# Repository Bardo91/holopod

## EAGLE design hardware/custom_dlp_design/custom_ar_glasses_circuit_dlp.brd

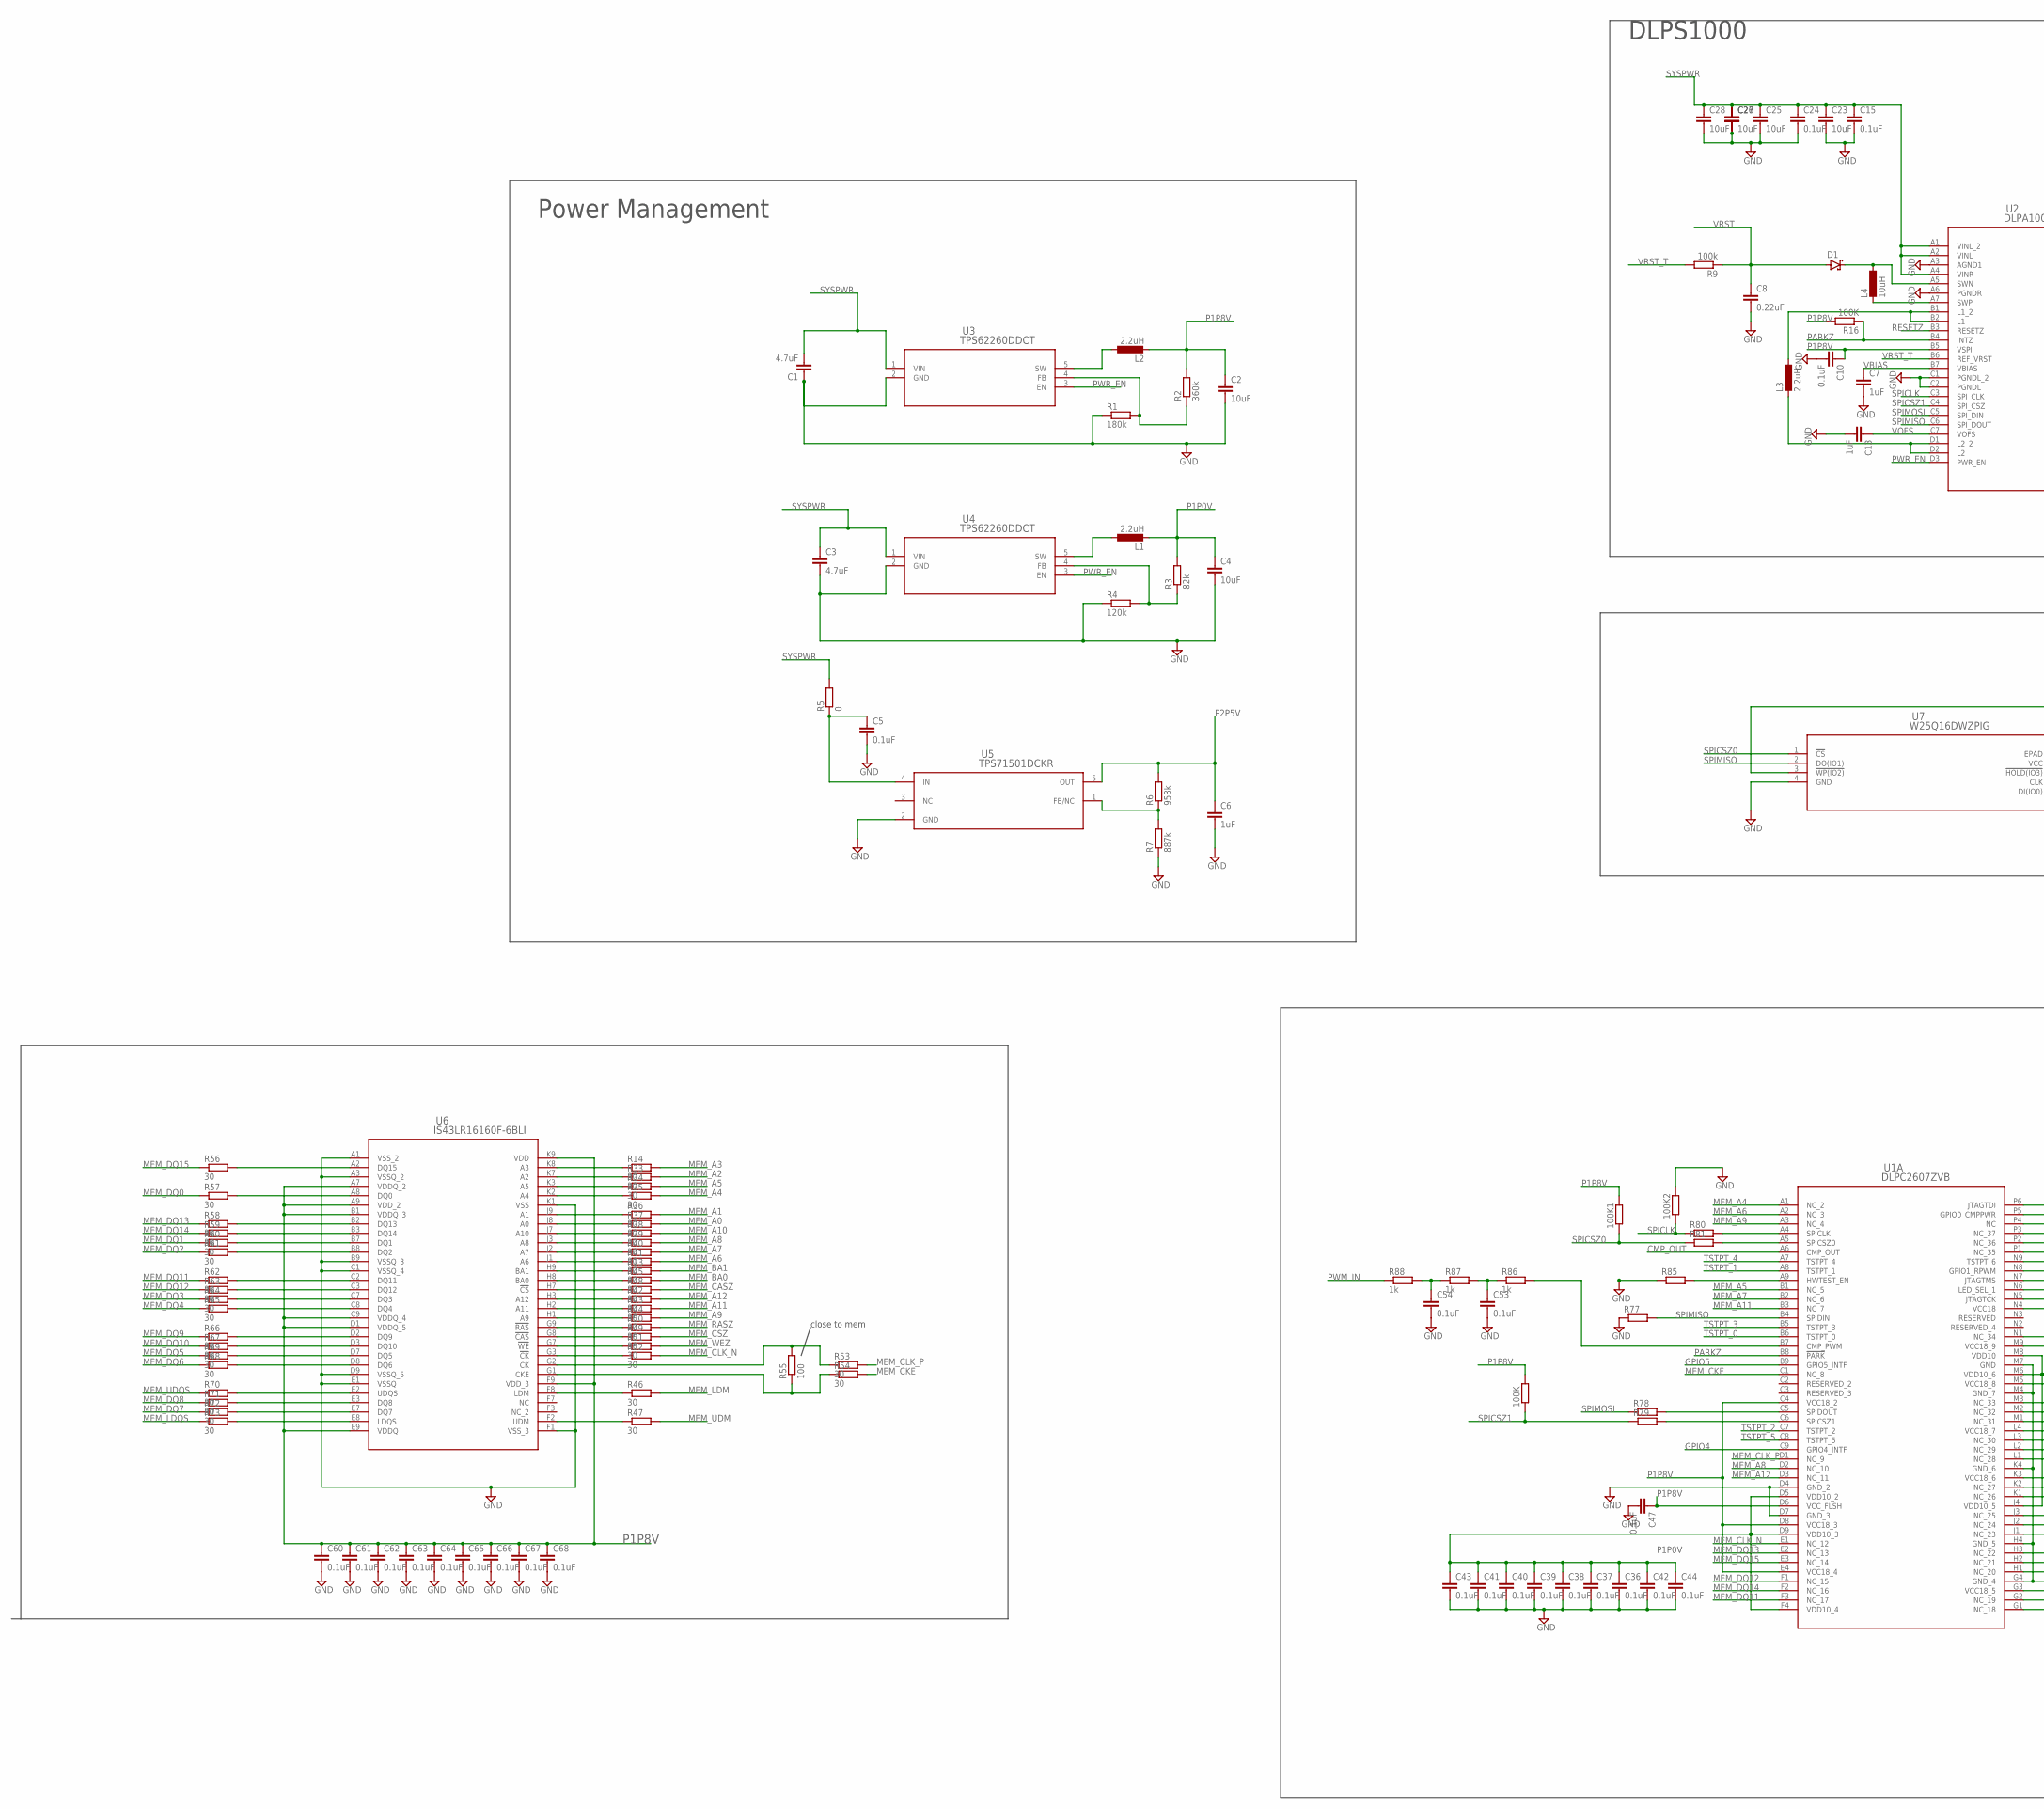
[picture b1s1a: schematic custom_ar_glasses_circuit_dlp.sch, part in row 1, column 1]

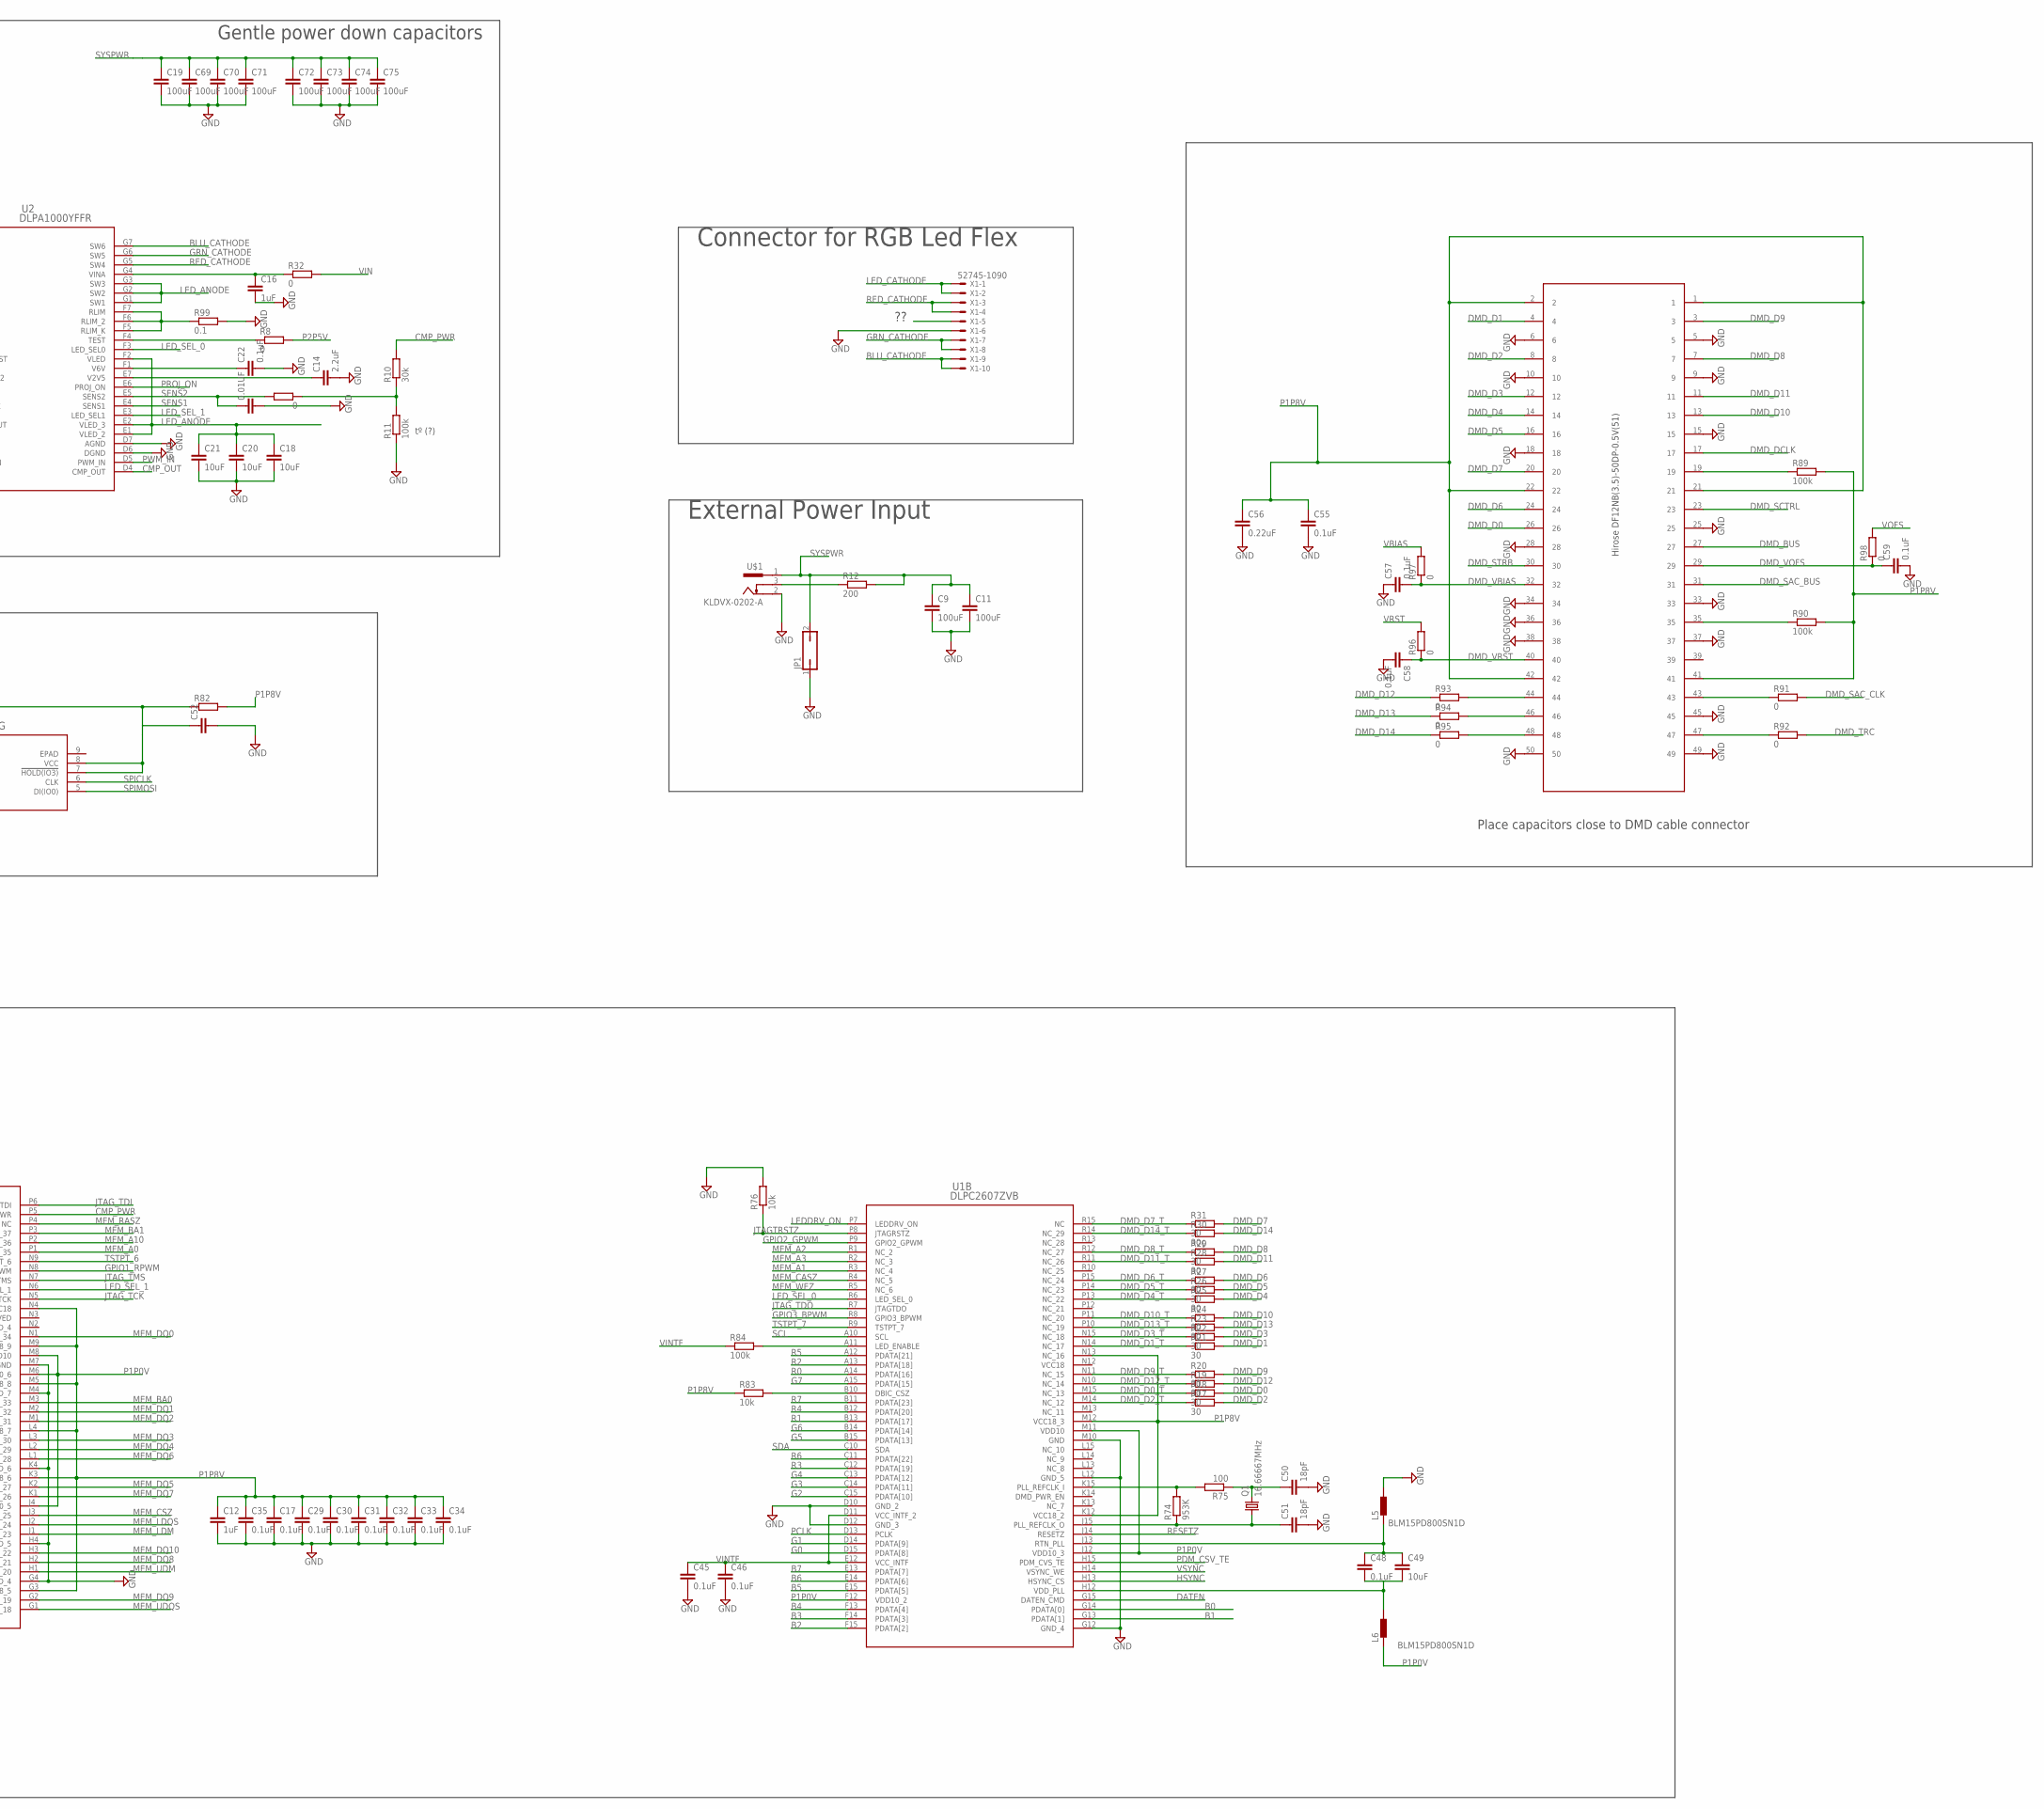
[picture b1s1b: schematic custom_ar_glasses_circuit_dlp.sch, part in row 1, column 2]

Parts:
0, 100K, 100K1, 100K2: R-EU_R0201; R0201
0.01UF: C-EUC0201; C0201
C1, C3: 4.7uF; C0201
C2, C4, C18, C20, C21, C23, C25, C27, C28, C49: 10uF; C0201
C5, C10, C15, C17, C22, C24, C29, C30, C31, C32, C33, C34, C35, C36, C37, C38, C39, C40, C41, C42, C43, C44, C45, C46, C47, C48, C53, C54, C55, C57, C58, C59, C60, C61, C62, C63, C64, C65, C66, C67, C68: 0.1uF; C0201
C6, C7, C12, C13, C16: 1uF; C0201
C8, C56: 0.22uF; C0201
C9, C11: 100uF; C1206K
C14: 2.2uF; C0201
C19, C69, C70, C71, C72, C73, C74, C75: 100uF; C0805
C26, C52: C-EUC0201; C0201
C50, C51: 18pF; C0201
D1: SCHOTTKY-DIODESMC; SMC
JP1: JP1Q; JP1
L1, L2, L3: 2.2uH; L3225M
L4: 10uH; L3216C
L5, L6: BLM15PD800SN1D; 0402
Q1: 16.66667MHz; MC-405
R1: 180k; R0201
R2: 360k; R0201
R3: 82k; R0201
R4: 120k; R0201
R5, R8, R32, R91, R92, R93, R94, R95, R96, R97, R98: 0; R0201
R6: 953k; R0201
R7: 887k; R0201
R9, R11, R84, R89, R90: 100k; R0201
R10: 30k; R0201
R12: 200; R1206
R13, R14, R17, R18, R19, R20, R21, R22, R23, R24, R25, R26, R27, R28, R29, R31, R33, R34, R35, R36, R37, R38, R39, R40, R41, R42, R43, R44, R45, R46, R47, R48, R49, R50, R51, R52, R53, R54, R56, R57, R58, R59, R60, R61, R62, R63, R64, R65, R66, R67, R68, R69, R70, R71, R72, R73: 30; R0201
R16: 100K; R0201
R30: 30ç; R0201
R55, R75: 100; R0201
R74: 953K; R0201
R76, R83: 10k; R0201
R77, R78, R79, R80, R81, R82, R85: R-EU_R0201; R0201
R86, R87, R88: 1k; R0201
R99: 0.1; R0201
U1: DLPC2607ZVB; ZVB176_TEX
U2: DLPA1000YFFR; YFF49_TEX
U3, U4: TPS62260DDCT; DDC5
U5: TPS71501DCKR; DCK5
U6: IS43LR16160F-6BLI; TFBGA-60_8X10_ISI
U7: W25Q16DWZPIG; WIN_ZP-8_WIN
U$1: KLDVX-0202-A
U$2: HIROSEDF12NB(3.5)-50DP-0.5V(51)
X1: 52745-1090

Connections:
B0: U1.G14 (PDATA[0])
B1: U1.G13 (PDATA[1])
B2: U1.F15 (PDATA[2])
B3: U1.F14 (PDATA[3])
B4: U1.F13 (PDATA[4])
B5: U1.E15 (PDATA[5])
B6: U1.E14 (PDATA[6])
B7: U1.E13 (PDATA[7])
BLU_CATHODE: U2.G7 (SW6), X1.9, X1.10
CMP_OUT: U1.A6 (CMP_OUT), U2.D4 (CMP_OUT)
CMP_PWR: R10.2, U1.P5 (GPIO0_CMPPWR)
DATEN: U1.G15 (DATEN_CMD)
DMD_BUS: U$2.27
DMD_D0: R18.2, U$2.26
DMD_D0_T: R18.1, U1.M15 (NC_13)
DMD_D1: R21.2, U$2.4
DMD_D1_T: R21.1, U1.N14 (NC_17)
DMD_D2: R17.2, U$2.8
DMD_D2_T: R17.1, U1.M14 (NC_12)
DMD_D3: R22.2, U$2.12
DMD_D3_T: R22.1, U1.N15 (NC_18)
DMD_D4: R25.2, U$2.14
DMD_D4_T: R25.1, U1.P13 (NC_22)
DMD_D5: R26.2, U$2.16
DMD_D5_T: R26.1, U1.P14 (NC_23)
DMD_D6: R27.2, U$2.24
DMD_D6_T: R27.1, U1.P15 (NC_24)
DMD_D7: R31.2, U$2.20
DMD_D7_T: R31.1, U1.R15 (NC)
DMD_D8: R29.2, U$2.7
DMD_D8_T: R29.1, U1.R12 (NC_27)
DMD_D9: R20.2, U$2.3
DMD_D9_T: R20.1, U1.N11 (NC_15)
DMD_D10: R24.2, U$2.13
DMD_D10_T: R24.1, U1.P11 (NC_20)
DMD_D11: R28.2, U$2.11
DMD_D11_T: R28.1, U1.R11 (NC_26)
DMD_D12: R19.2, R93.1
DMD_D12_T: R19.1, U1.N10 (NC_14)
DMD_D13: R23.2, R94.1
DMD_D13_T: R23.1, U1.P10 (NC_19)
DMD_D14: R30.2, R95.1
DMD_D14_T: R30.1, U1.R14 (NC_29)
DMD_DCLK: U$2.17
DMD_SAC_BUS: U$2.31
DMD_SAC_CLK: R91.2
DMD_SCTRL: U$2.23
DMD_STRB: U$2.30
DMD_TRC: R92.2
DMD_VBIAS: C57.2, R97.1, U$2.32
DMD_VOFS: C59.1, R98.1, U$2.29
DMD_VRST: C58.1, R96.1, U$2.40
G0: U1.D15 (PDATA[8])
G1: U1.D14 (PDATA[9])
G2: U1.C15 (PDATA[10])
G3: U1.C14 (PDATA[11])
G4: U1.C13 (PDATA[12])
G5: U1.B15 (PDATA[13])
G6: U1.B14 (PDATA[14])
G7: U1.A15 (PDATA[15])
GND: 0.01UF.2, 100K2.2, C1.1, C2.2, C3.2, C4.2, C5.2, C6.2, C7.2, C8.2, C9.2, C10.2, C11.2, C12.2, C13.2, C14.2, C15.2, C16.2, C17.2, C18.2, C19.2, C20.2, C21.2, C22.2, C23.2, C24.2, C25.2, C26.2, C27.2, C28.2, C29.2, C30.2, C31.2, C32.2, C33.2, C34.2, C35.2, C36.2, C37.2, C38.2, C39.2, C40.2, C41.2, C42.2, C43.2, C44.2, C45.2, C46.2, C47.2, C50.2, C51.2, C52.2, C53.2, C54.2, C55.2, C56.2, C57.1, C58.2, C59.2, C60.2, C61.2, C62.2, C63.2, C64.2, C65.2, C66.2, C67.2, C68.2, C69.2, C70.2, C71.2, C72.2, C73.2, C74.2, C75.2, JP1.1, L5.2, R1.1, R4.1, R7.1, R11.1, R76.2, R77.1, R85.1, R99.2, U1.D4 (GND_2), U1.D7 (GND_3), U1.D10 (GND_2), U1.D12 (GND_3), U1.G4 (GND_4), U1.G12 (GND_4), U1.H4 (GND_5), U1.K4 (GND_6), U1.L12 (GND_5), U1.M4 (GND_7), U1.M7 (GND), U1.M10 (GND), U2.A3 (AGND1), U2.A6 (PGNDR), U2.C1 (PGNDL_2), U2.C2 (PGNDL), U2.D6 (DGND), U2.D7 (AGND), U3.2 (GND), U4.2 (GND), U5.2 (GND), U6.A1 (VSS_2), U6.A3 (VSSQ_2), U6.B9 (VSSQ_3), U6.C1 (VSSQ_4), U6.D9 (VSSQ_5), U6.E1 (VSSQ), U6.F1 (VSS_3), U6.K1 (VSS), U7.4 (GND), U$1.2, U$2.5, U$2.6, U$2.9, U$2.10, U$2.15, U$2.18, U$2.25, U$2.28, U$2.33, U$2.34, U$2.36, U$2.37, U$2.38, U$2.45, U$2.49, U$2.50, X1.6
GPIO1_RPWM: U1.N8 (GPIO1_RPWM)
GPIO2_GPWM: U1.P9 (GPIO2_GPWM)
GPIO3_BPWM: U1.R8 (GPIO3_BPWM)
GPIO4: U1.C9 (GPIO4_INTF)
GPIO5: U1.B9 (GPIO5_INTF)
GRN_CATHODE: U2.G6 (SW5), X1.7, X1.8
HSYNC: U1.H13 (HSYNC_CS)
JTAGTRSTZ: R76.1, U1.P8 (JTAGRSTZ)
JTAG_TCK: U1.N5 (JTAGTCK)
JTAG_TDI: U1.P6 (JTAGTDI)
JTAG_TDO: U1.R7 (JTAGTDO)
JTAG_TMS: U1.N7 (JTAGTMS)
LEDDRV_ON: U1.P7 (LEDDRV_ON)
LED_ANODE: C18.1, C20.1, C21.1, U2.E1 (VLED_2), U2.E2 (VLED_3), U2.F2 (VLED), U2.G1 (SW1), U2.G2 (SW2), U2.G3 (SW3)
LED_CATHODE: X1.1, X1.2
LED_SEL_0: U1.R6 (LED_SEL_0), U2.F3 (LED_SEL0)
LED_SEL_1: U1.N6 (LED_SEL_1), U2.E3 (LED_SEL1)
MEM_A0: R37.2, U1.P1 (NC_35)
MEM_A1: R36.2, U1.R3 (NC_4)
MEM_A2: R33.2, U1.R1 (NC_2)
MEM_A3: R14.2, U1.R2 (NC_3)
MEM_A4: R35.2, U1.A1 (NC_2)
MEM_A5: R34.2, U1.B1 (NC_5)
MEM_A6: R41.2, U1.A2 (NC_3)
MEM_A7: R40.2, U1.B2 (NC_6)
MEM_A8: R39.2, U1.D2 (NC_10)
MEM_A9: R44.2, U1.A3 (NC_4)
MEM_A10: R38.2, U1.P2 (NC_36)
MEM_A11: R43.2, U1.B3 (NC_7)
MEM_A12: R42.2, U1.D3 (NC_11)
MEM_BA0: R45.2, U1.M3 (NC_33)
MEM_BA1: R13.2, U1.P3 (NC_37)
MEM_CASZ: R48.2, U1.R4 (NC_5)
MEM_CKE: R54.2, U1.C1 (NC_8)
MEM_CLK_N: R52.2, U1.E1 (NC_12)
MEM_CLK_P: R53.2, U1.D1 (NC_9)
MEM_CSZ: R49.2, U1.J3 (NC_25)
MEM_DQ0: R57.1, U1.N1 (NC_34)
MEM_DQ1: R60.1, U1.M2 (NC_32)
MEM_DQ2: R61.1, U1.M1 (NC_31)
MEM_DQ3: R64.1, U1.L3 (NC_30)
MEM_DQ4: R65.1, U1.L2 (NC_29)
MEM_DQ5: R69.1, U1.K2 (NC_27)
MEM_DQ6: R68.1, U1.L1 (NC_28)
MEM_DQ7: R72.1, U1.K1 (NC_26)
MEM_DQ8: R71.1, U1.H2 (NC_21)
MEM_DQ9: R66.1, U1.G2 (NC_19)
MEM_DQ10: R67.1, U1.H3 (NC_22)
MEM_DQ11: R62.1, U1.F3 (NC_17)
MEM_DQ12: R63.1, U1.F1 (NC_15)
MEM_DQ13: R58.1, U1.E2 (NC_13)
MEM_DQ14: R59.1, U1.F2 (NC_16)
MEM_DQ15: R56.1, U1.E3 (NC_14)
MEM_LDM: R46.2, U1.J1 (NC_23)
MEM_LDQS: R73.1, U1.J2 (NC_24)
MEM_RASZ: R50.2, U1.P4 (NC)
MEM_UDM: R47.2, U1.H1 (NC_20)
MEM_UDQS: R70.1, U1.G1 (NC_18)
MEM_WEZ: R51.2, U1.R5 (NC_6)
unnamed: R1.2, R2.1, U3.4 (FB)
unnamed: C22.1, U2.F1 (V6V)
unnamed: L2.1, U3.5 (SW)
unnamed: R8.1, U2.F4 (TEST)
unnamed: L1.1, U4.5 (SW)
unnamed: R99.1, U2.F5 (RLIM_K), U2.F6 (RLIM_2), U2.F7 (RLIM)
unnamed: R3.1, R4.2, U4.4 (FB)
unnamed: C5.1, R5.1, U5.4 (IN)
unnamed: C14.1, U2.E7 (V2V5)
unnamed: R6.1, R7.2, U5.1 (FB/NC)
unnamed: L4.2, U2.A7 (SWP)
unnamed: D1.C, L4.1, U2.A5 (SWN)
unnamed: R36.1, U6.J9 (A1)
unnamed: 0.1, R10.1, R11.2
unnamed: R12.1, U$1.3
unnamed: C16.1, R32.1, U2.G4 (VINA)
unnamed: R35.1, U6.K2 (A4)
unnamed: C48.1, C49.1, L5.1, U1.J13 (RTN_PLL)
unnamed: C48.2, C49.2, L6.2, U1.H12 (VDD_PLL)
unnamed: R14.1, U6.K8 (A3)
unnamed: R13.1, U6.H9 (BA1)
unnamed: R34.1, U6.K3 (A5)
unnamed: R33.1, U6.K7 (A2)
unnamed: L3.1, U2.B1 (L1_2), U2.B2 (L1)
unnamed: L3.2, U2.D1 (L2_2), U2.D2 (L2)
unnamed: R40.1, U6.J2 (A7)
unnamed: R39.1, U6.J3 (A8)
unnamed: R38.1, U6.J7 (A10)
unnamed: R43.1, U6.H2 (A11)
unnamed: R37.1, U6.J8 (A0)
unnamed: R41.1, U6.J1 (A6)
unnamed: R42.1, U6.H3 (A12)
unnamed: R44.1, U6.H1 (A9)
unnamed: R45.1, U6.H8 (BA0)
unnamed: R46.1, U6.F8 (LDM)
unnamed: R47.1, U6.F2 (UDM)
unnamed: R49.1, U6.G8 (!CAS)
unnamed: R48.1, U6.H7 (!CS)
unnamed: R50.1, U6.G9 (!RAS)
unnamed: R51.1, U6.G7 (!WE)
unnamed: R52.1, U6.G3 (!CK)
unnamed: R53.1, R55.2, U6.G2 (CK)
unnamed: R54.1, R55.1, U6.G1 (CKE)
unnamed: R74.2, R75.2, U1.K15 (PLL_REFCLK_I)
unnamed: C51.1, Q1.1, R74.1, U1.J15 (PLL_REFCLK_O)
unnamed: C50.1, Q1.2, R75.1
unnamed: R78.2, U1.C5 (SPIDOUT)
unnamed: R79.2, U1.C6 (SPICSZ1)
unnamed: R80.2, U1.A4 (SPICLK)
unnamed: R56.2, U6.A2 (DQ15)
unnamed: R57.2, U6.A8 (DQ0)
unnamed: R58.2, U6.B2 (DQ13)
unnamed: R59.2, U6.B3 (DQ14)
unnamed: R60.2, U6.B7 (DQ1)
unnamed: R61.2, U6.B8 (DQ2)
unnamed: R62.2, U6.C2 (DQ11)
unnamed: R63.2, U6.C3 (DQ12)
unnamed: R64.2, U6.C7 (DQ3)
unnamed: R65.2, U6.C8 (DQ4)
unnamed: R66.2, U6.D2 (DQ9)
unnamed: R67.2, U6.D3 (DQ10)
unnamed: R69.2, U6.D7 (DQ5)
unnamed: R68.2, U6.D8 (DQ6)
unnamed: R71.2, U6.E3 (DQ8)
unnamed: R72.2, U6.E7 (DQ7)
unnamed: R70.2, U6.E2 (UDQS)
unnamed: R73.2, U6.E8 (LDQS)
unnamed: R81.2, U1.A5 (SPICSZ0)
unnamed: R84.2, U1.A11 (LED_ENABLE)
unnamed: R85.2, U1.A9 (HWTEST_EN)
unnamed: C52.1, R82.1, U7.3 (!WP(IO2)), U7.7 (!HOLD(IO3)), U7.8 (VCC)
unnamed: R83.2, U1.B10 (DBIC_CSZ)
unnamed: R86.2, U1.B7 (CMP_PWM)
unnamed: C54.1, R87.1, R88.2
unnamed: C53.1, R86.1, R87.2
unnamed: R90.1, U$2.35
unnamed: R89.1, U$2.19
unnamed: R91.1, U$2.43
unnamed: R92.1, U$2.47
unnamed: R93.2, U$2.44
unnamed: R94.2, U$2.46
unnamed: R95.2, U$2.48
P1P0V: C4.1, C36.1, C37.1, C38.1, C39.1, C40.1, C41.1, C42.1, C43.1, C44.1, L1.2, L6.1, R3.2, U1.D5 (VDD10_2), U1.D9 (VDD10_3), U1.F4 (VDD10_4), U1.F12 (VDD10_2), U1.J4 (VDD10_5), U1.J12 (VDD10_3), U1.M6 (VDD10_6), U1.M8 (VDD10), U1.M11 (VDD10)
P1P8V: 100K.2, 100K1.2, C2.1, C10.1, C12.1, C17.1, C29.1, C30.1, C31.1, C32.1, C33.1, C34.1, C35.1, C47.1, C55.1, C56.1, C60.1, C61.1, C62.1, C63.1, C64.1, C65.1, C66.1, C67.1, C68.1, L2.2, R2.2, R16.2, R82.2, R83.1, R89.2, R90.2, U1.C4 (VCC18_2), U1.D6 (VCC_FLSH), U1.D8 (VCC18_3), U1.E4 (VCC18_4), U1.G3 (VCC18_5), U1.K3 (VCC18_6), U1.K12 (VCC18_2), U1.L4 (VCC18_7), U1.M5 (VCC18_8), U1.M9 (VCC18_9), U1.M12 (VCC18_3), U1.N4 (VCC18), U1.N13 (NC_16), U2.B5 (VSPI), U6.A7 (VDDQ_2), U6.A9 (VDD_2), U6.B1 (VDDQ_3), U6.C9 (VDDQ_4), U6.D1 (VDDQ_5), U6.E9 (VDDQ), U6.F9 (VDD_3), U6.K9 (VDD), U$2.1, U$2.2, U$2.21, U$2.22, U$2.41, U$2.42
P2P5V: C6.1, R6.2, R8.2, U5.5 (OUT)
PARKZ: R16.1, U1.B8 (!PARK), U2.B4 (INTZ)
PCLK: U1.D13 (PCLK)
PDM_CSV_TE: U1.H15 (PDM_CVS_TE)
PROJ_ON: U2.E6 (PROJ_ON)
PWM_IN: R88.1, U2.D5 (PWM_IN)
PWR_EN: U2.D3 (PWR_EN), U3.3 (EN), U4.3 (EN)
R0: U1.A14 (PDATA[16])
R1: U1.B13 (PDATA[17])
R2: U1.A13 (PDATA[18])
R3: U1.C12 (PDATA[19])
R4: U1.B12 (PDATA[20])
R5: U1.A12 (PDATA[21])
R6: U1.C11 (PDATA[22])
R7: U1.B11 (PDATA[23])
RED_CATHODE: U2.G5 (SW4), X1.3, X1.4
RESETZ: U1.J14 (RESETZ), U2.B3 (RESETZ)
SCL: U1.A10 (SCL)
SDA: U1.C10 (SDA)
SENS1: U2.E4 (SENS1)
SENS2: 0.2, 0.01UF.1, U2.E5 (SENS2)
SPICLK: 100K2.1, R80.1, U2.C3 (SPI_CLK), U7.6 (CLK)
SPICSZ0: 100K1.1, R81.1, U7.1 (!CS)
SPICSZ1: 100K.1, R79.1, U2.C4 (SPI_CSZ)
SPIMISO: R77.2, U1.B4 (SPIDIN), U2.C6 (SPI_DOUT), U7.2 (DO(IO1))
SPIMOSI: R78.1, U2.C5 (SPI_DIN), U7.5 (DI(IO0))
SYSPWR: C1.2, C3.1, C9.1, C11.1, C15.1, C19.1, C23.1, C24.1, C25.1, C26.1, C27.1, C28.1, C69.1, C70.1, C71.1, C72.1, C73.1, C74.1, C75.1, JP1.2, R5.2, R12.2, U2.A1 (VINL_2), U2.A2 (VINL), U2.A4 (VINR), U3.1 (VIN), U4.1 (VIN), U$1.1
TSTPT_0: U1.B6 (TSTPT_0)
TSTPT_1: U1.A8 (TSTPT_1)
TSTPT_2: U1.C7 (TSTPT_2)
TSTPT_3: U1.B5 (TSTPT_3)
TSTPT_4: U1.A7 (TSTPT_4)
TSTPT_5: U1.C8 (TSTPT_5)
TSTPT_6: U1.N9 (TSTPT_6)
TSTPT_7: U1.R9 (TSTPT_7)
VBIAS: C7.1, R97.2, U2.B7 (VBIAS)
VCC18: U1.N12 (VCC18)
VIN: R32.2
VINTF: C45.1, C46.1, R84.1, U1.D11 (VCC_INTF_2), U1.E12 (VCC_INTF)
VOFS: C13.1, R98.2, U2.C7 (VOFS)
VRST: C8.1, D1.A, R9.1, R96.2
VRST_T: R9.2, U2.B6 (REF_VRST)
VSYNC: U1.H14 (VSYNC_WE)

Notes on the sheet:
Power Management
close to mem
Place capacitors close to DMD cable connector
External Power Input
Connector for RGB Led Flex
tº (?)
Gentle power down capacitors
DLPS1000

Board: 2 copper layers, 197 parts (0 on the bottom side), 187 nets, no tracks yet.

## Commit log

2021-12-09 Initialized repo with some files

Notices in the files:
parts and their libraries:
COPYRIGHT: Copyright (C) 2018 Accelerated Designs. All rights reserved
COPYRIGHT: Copyright (C) 2021 Ultra Librarian. All rights reserved.
